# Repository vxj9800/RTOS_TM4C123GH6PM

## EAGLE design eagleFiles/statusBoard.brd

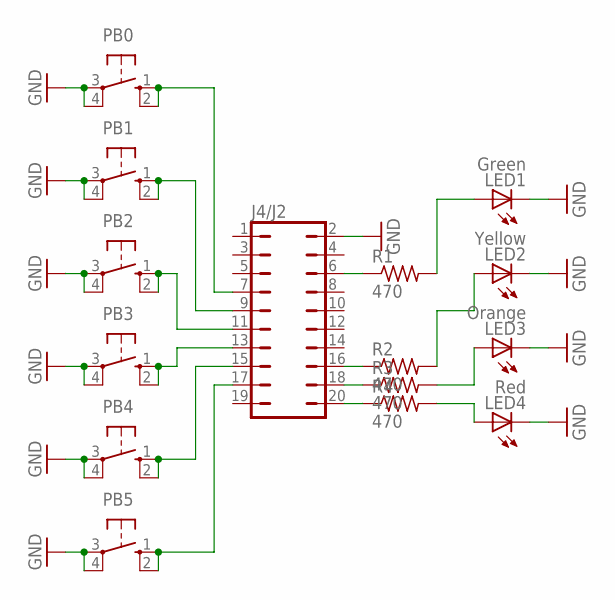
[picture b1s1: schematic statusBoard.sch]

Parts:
J4/J2: JP10Q
LED1: Green; LED3MM
LED2: Yellow; LED3MM
LED3: Orange; LED3MM
LED4: Red; LED3MM
PB0, PB1, PB2, PB3, PB4, PB5: 10-XX; B3F-10XX
R1, R2, R3, R4: 470; 0204/7

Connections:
GND: J4/J2.2, LED1.K (C), LED2.K (C), LED3.K (C), LED4.K (C), PB0.3, PB0.4 (P1), PB1.3, PB1.4 (P1), PB2.3, PB2.4 (P1), PB3.3, PB3.4 (P1), PB4.3, PB4.4 (P1), PB5.3, PB5.4 (P1)
unnamed: J4/J2.6, R1.1
unnamed: LED1.A, R1.2
unnamed: J4/J2.16, R2.1
unnamed: J4/J2.18, R3.1
unnamed: J4/J2.20, R4.1
unnamed: LED2.A, R2.2
unnamed: LED3.A, R3.2
unnamed: LED4.A, R4.2
unnamed: J4/J2.7, PB0.1 (S), PB0.2 (S1)
unnamed: J4/J2.9, PB1.1 (S), PB1.2 (S1)
unnamed: J4/J2.11, PB2.1 (S), PB2.2 (S1)
unnamed: J4/J2.13, PB3.1 (S), PB3.2 (S1)
unnamed: J4/J2.15, PB4.1 (S), PB4.2 (S1)
unnamed: J4/J2.17, PB5.1 (S), PB5.2 (S1)

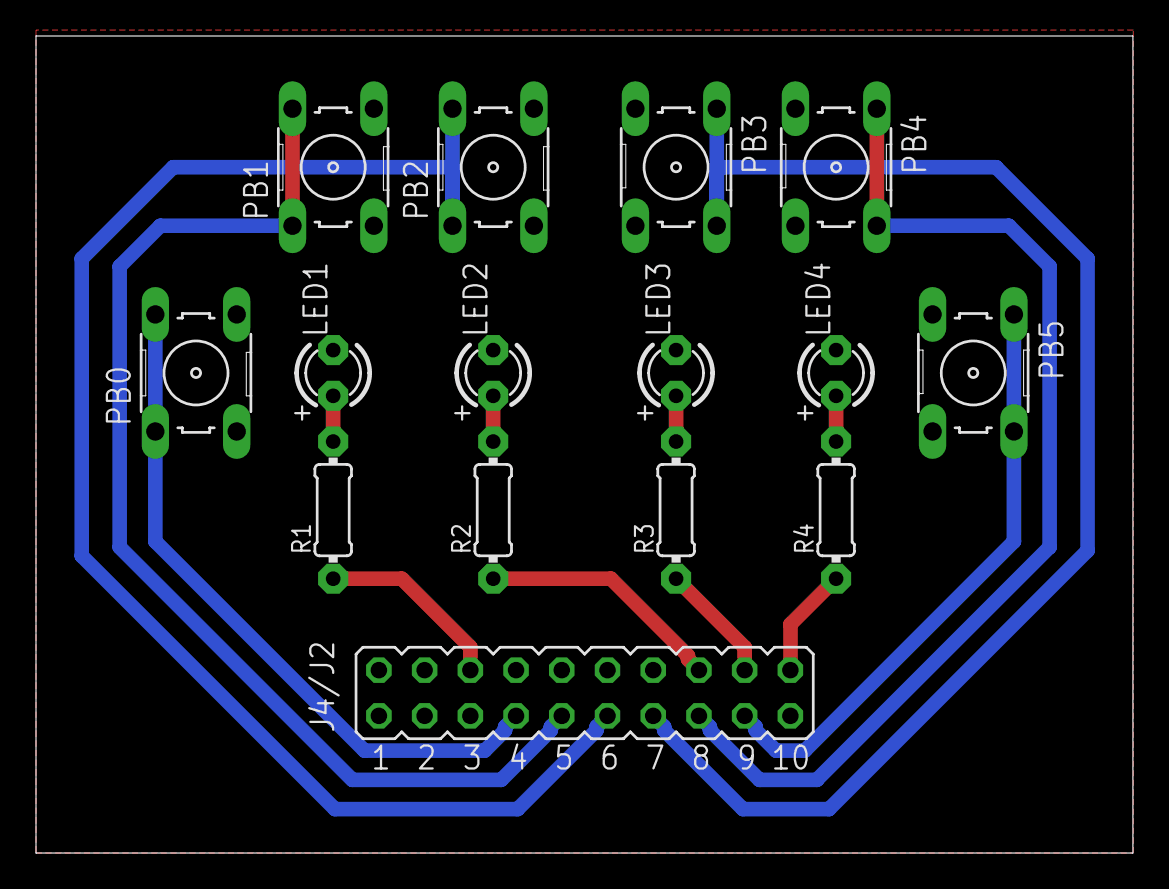
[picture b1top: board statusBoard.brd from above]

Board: 2 copper layers, 60.9 x 45.4 mm, 15 parts (0 on the bottom side), 15 nets.

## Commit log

2021-05-20 Added all the project files
2021-07-31 Add eagle files for the status board
    The status board is basically a couple of push buttons and LEDs. The LEDs represent the execution of different tasks while the push buttons either start a task, stop a task or cause a semaphore reque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
